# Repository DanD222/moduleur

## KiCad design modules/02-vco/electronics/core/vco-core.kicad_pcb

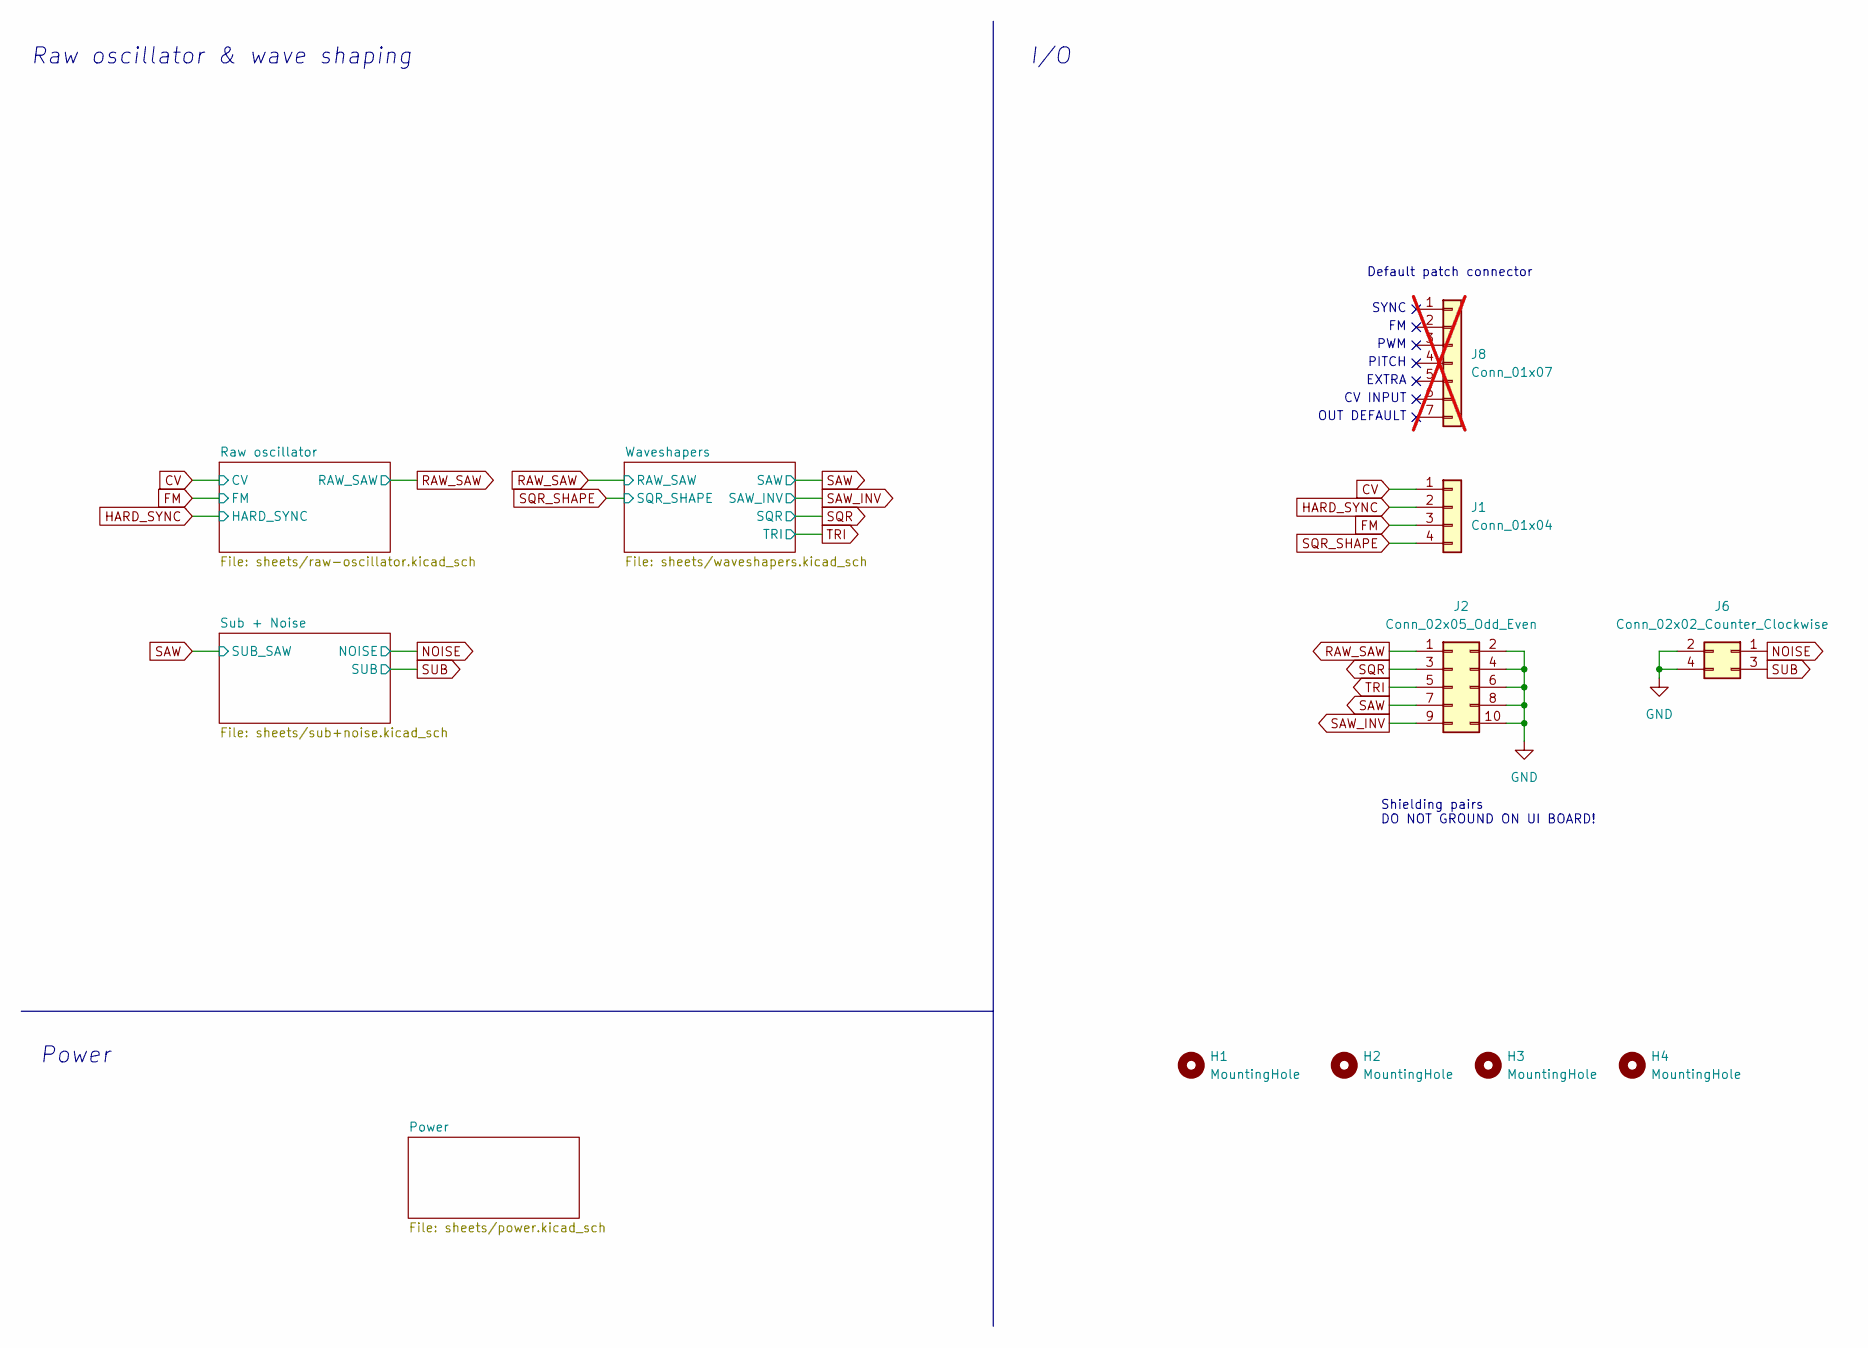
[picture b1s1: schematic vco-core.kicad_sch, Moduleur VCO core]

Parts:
H1, H2, H3, H4: MountingHole; MountingHole_3.2mm_M3_DIN965_Pad
J1: Conn_01x04; PinHeader_1x04_P2.54mm_Vertical; Mouser Part no. 200-HTSW10407TS
J2: Conn_02x05_Odd_Even; PinHeader_2x05_P2.54mm_Vertical; Mouser Part no. 200-TSW10507TD
J6: Conn_02x02_Counter_Clockwise; PinHeader_2x02_P2.54mm_Vertical; Mouser Part no. 200-HTSW10207TD
J8: Conn_01x07; PinHeader_1x07_P2.54mm_Vertical; Mouser Part no. 474-PRT-09280; not fitted

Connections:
CV: J1.1; also elsewhere on the board
FM: J1.3; also elsewhere on the board
GND: J2.2, J2.4, J2.6, J2.8, J2.10, J6.2, J6.4; also elsewhere on the board
HARD_SYNC: J1.2; also elsewhere on the board
NOISE: J6.1; also elsewhere on the board
RAW_SAW: J2.1; also elsewhere on the board
SAW: J2.7; also elsewhere on the board
SAW_INV: J2.9; also elsewhere on the board
SQR: J2.3; also elsewhere on the board
SUB: J6.3; also elsewhere on the board
TRI: J2.5; also elsewhere on the board

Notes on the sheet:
Power
PWM
Default patch connector
CV INPUT
SYNC
OUT DEFAULT
Shielding pairs DO NOT GROUND ON UI BOARD!
EXTRA
Raw oscillator & wave shaping
I/O
PITCH

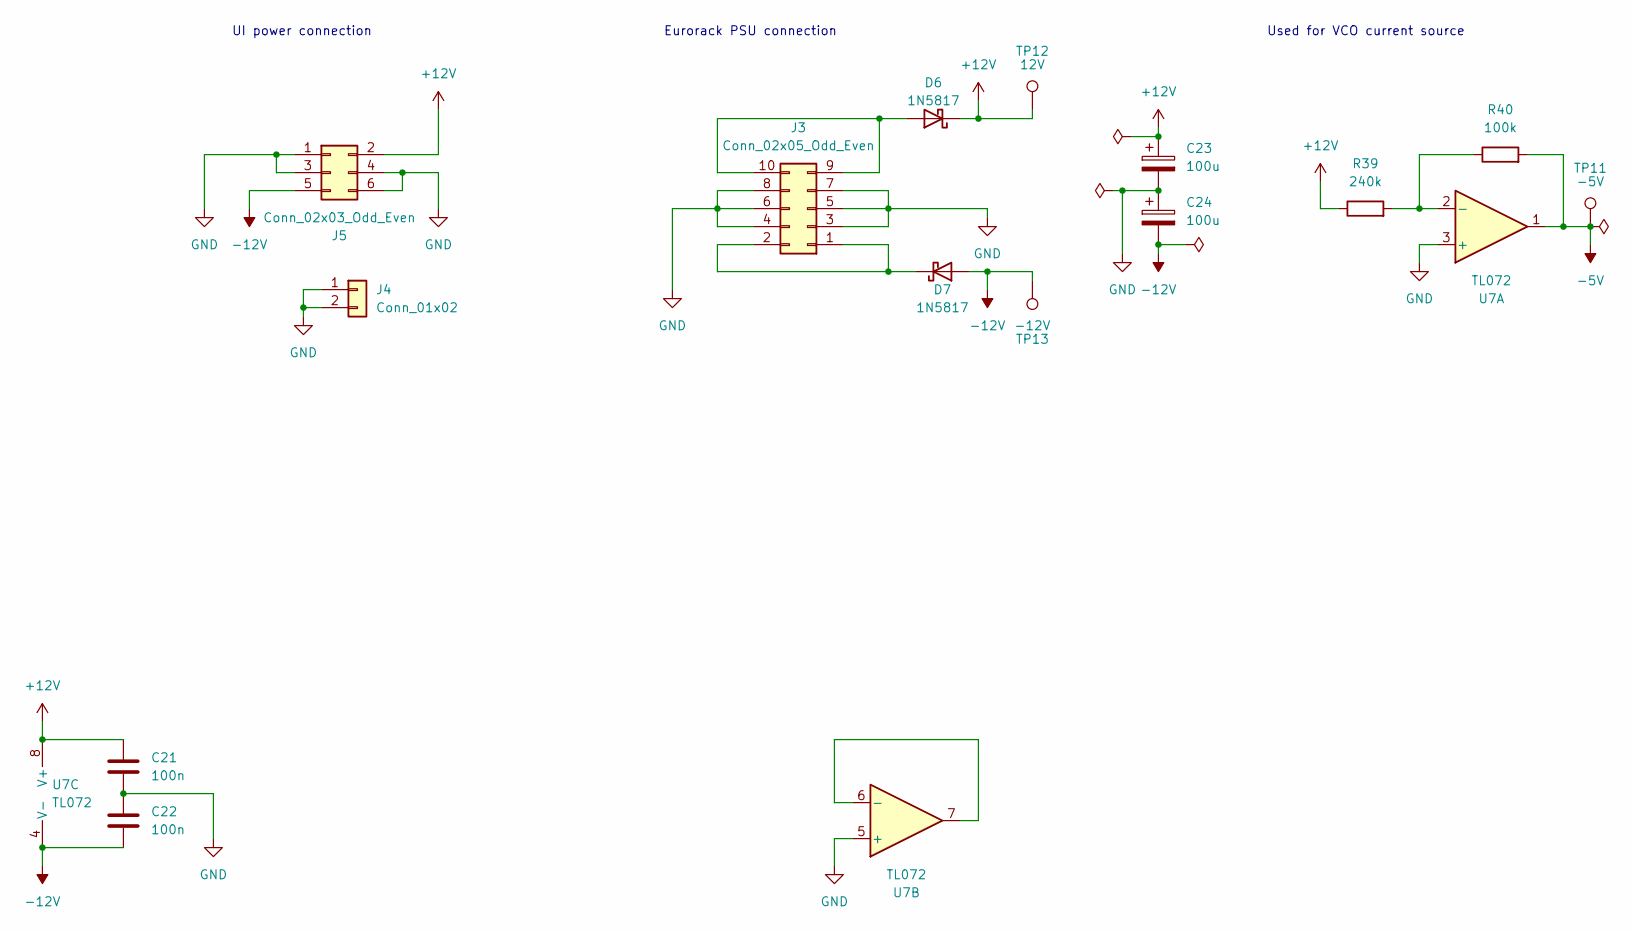
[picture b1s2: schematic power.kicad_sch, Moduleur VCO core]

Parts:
C21, C22: 100n; C_0603_1608Metric; LCSC C14663
C23, C24: 100u; CP_Elec_6.3x7.7; LCSC C2836442
D6, D7: 1N5817; D_SOD-323; LCSC C5190152
J3: Conn_02x05_Odd_Even; IDC-Header_2x05_P2.54mm_Horizontal; Mouser Part no. 571-5103310-1
J4: Conn_01x02; PinHeader_1x02_P2.54mm_Vertical; Mouser Part no. 200-HTSW10207TS
J5: Conn_02x03_Odd_Even; PinHeader_2x03_P2.54mm_Vertical; Mouser Part no. 200-TSW10307TD
R39: 240k; R_0603_1608Metric; LCSC C4197
R40: 100k; R_0603_1608Metric; LCSC C25803
TP11: -5V; TestPoint_THTPad_2.0x2.0mm_Drill1.0mm
TP12: 12V; TestPoint_THTPad_2.0x2.0mm_Drill1.0mm
TP13: -12V; TestPoint_THTPad_2.0x2.0mm_Drill1.0mm
U7: TL072; SOIC-8_3.9x4.9mm_P1.27mm; LCSC C6961

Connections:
-5V: R40.2, TP11.1 (1_1), U7.1; also elsewhere on the board
GND: C21.2, C22.1, C23.2, C24.1, J3.3, J3.4, J3.5, J3.6, J3.7, J3.8, J4.1, J4.2, J5.1, J5.3, J5.4, J5.6, U7.3 (+), U7.5 (+); also elsewhere on the board
unnamed: D6.2 (A), J3.9, J3.10
unnamed: D7.1 (K), J3.1, J3.2
unnamed: R39.2, R40.1, U7.2 (-)
unnamed: U7.6 (-), U7.7

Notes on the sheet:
UI power connection
Eurorack PSU connection
Used for VCO current source

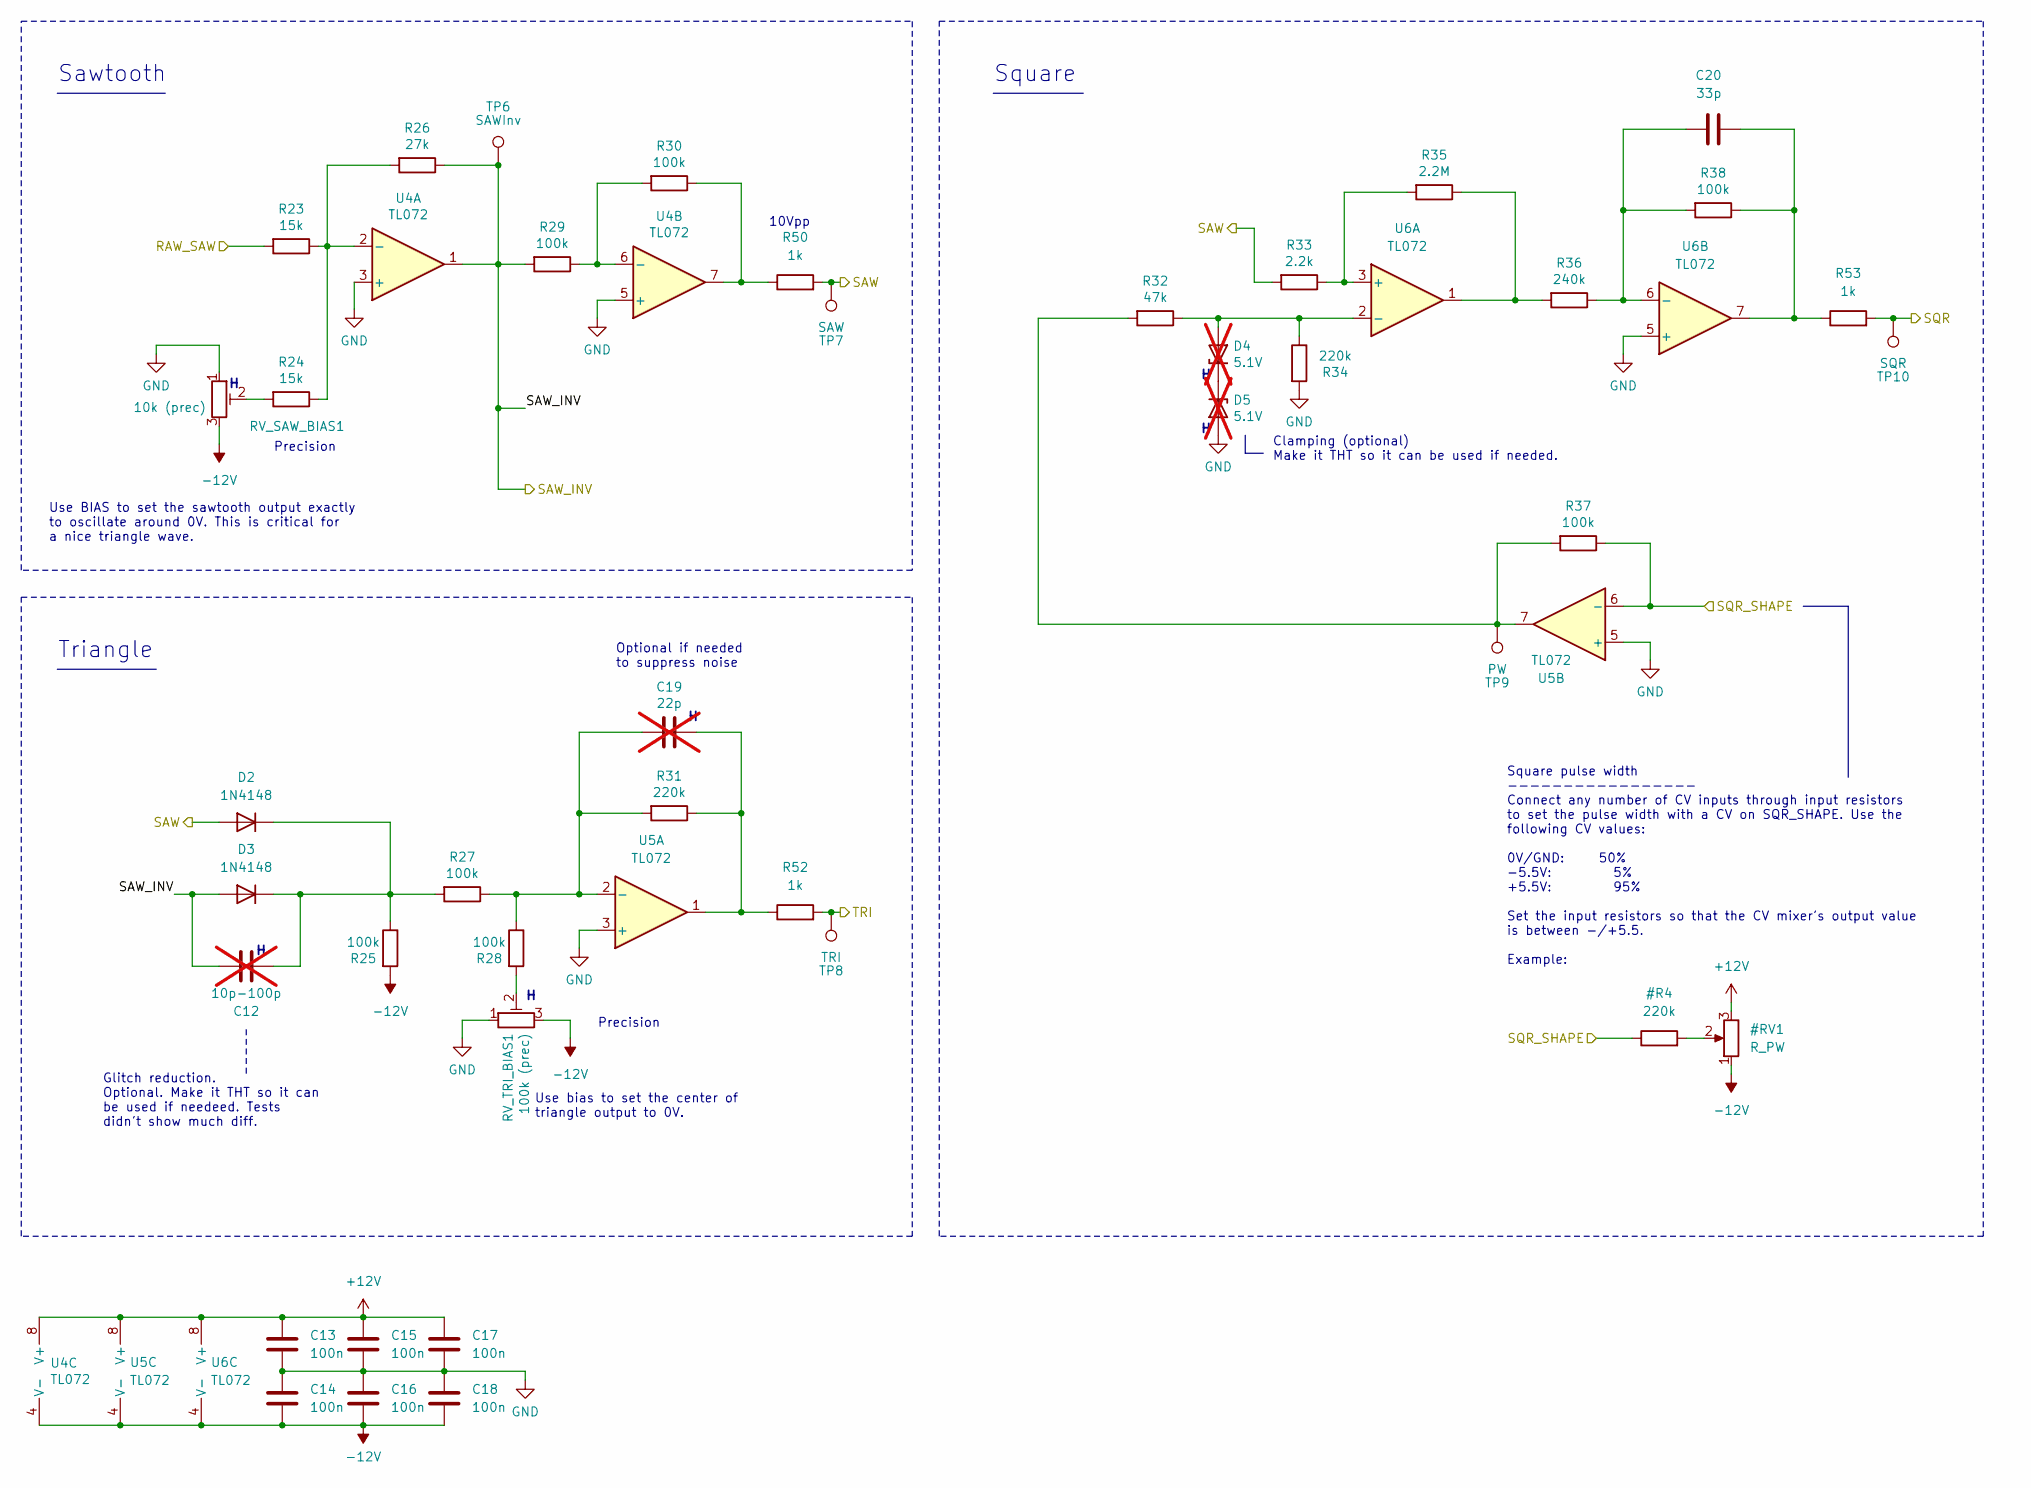
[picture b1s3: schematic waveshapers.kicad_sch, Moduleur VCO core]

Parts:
C12: 10p-100p; C_Rect_L7.0mm_W2.5mm_P5.00mm; not fitted
C13, C14, C15, C16, C17, C18: 100n; C_0603_1608Metric; LCSC C14663
C19: 22p; C_Disc_D3.0mm_W2.0mm_P2.50mm; not fitted
C20: 33p; C_0603_1608Metric; LCSC C1663
D2, D3: 1N4148; D_SOD-123; LCSC C81598
D4, D5: 5.1V; D_DO-34_SOD68_P2.54mm_Vertical_AnodeUp; not fitted
R23, R24: 15k; R_0603_1608Metric; LCSC C22809
R25, R27, R28, R29, R30, R37, R38: 100k; R_0603_1608Metric; LCSC C25803
R26: 27k; R_0603_1608Metric; LCSC C22967
R31, R34: 220k; R_0603_1608Metric; LCSC C22961
R32: 47k; R_0603_1608Metric; LCSC C25819
R33: 2.2k; R_0603_1608Metric; LCSC C4190
R35: 2.2M; R_0603_1608Metric; LCSC C18679
R36: 240k; R_0603_1608Metric; LCSC C4197
R50, R52, R53: 1k; R_0603_1608Metric; LCSC C21190
RV_SAW_BIAS1: 10k (prec); Potentiometer_Bourns_3006P_Horizontal; Mouser Part no. 652-3006P-1-103-LF
RV_TRI_BIAS1: 100k (prec); Potentiometer_Bourns_3006P_Horizontal; Mouser Part no. 652-3006P-1-104-LF
TP6: SAWInv; TestPoint_THTPad_2.0x2.0mm_Drill1.0mm
TP7: SAW; TestPoint_THTPad_2.0x2.0mm_Drill1.0mm
TP8: TRI; TestPoint_THTPad_2.0x2.0mm_Drill1.0mm
TP9: PW; TestPoint_THTPad_2.0x2.0mm_Drill1.0mm
TP10: SQR; TestPoint_THTPad_2.0x2.0mm_Drill1.0mm
U4, U5, U6: TL072; SOIC-8_3.9x4.9mm_P1.27mm; LCSC C6961

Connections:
GND: C13.2, C14.1, C15.2, C16.1, C17.2, C18.1, D5.2 (A), R34.2, RV_SAW_BIAS1.1, RV_TRI_BIAS1.1, U4.3 (+), U4.5 (+), U5.3 (+), U5.5 (+), U6.5 (+); also elsewhere on the board
unnamed: C19.1, R31.1, R52.1, U5.1
unnamed: C20.2, R38.1, R53.1, U6.7
unnamed: C12.1, D2.1 (K), D3.1 (K), R25.1, R27.2
unnamed: D4.2 (A), R32.1, R34.1, U6.2 (-)
unnamed: D4.1 (K), D5.1 (K)
unnamed: R24.2, RV_SAW_BIAS1.2
unnamed: R28.2, RV_TRI_BIAS1.2
unnamed: R30.1, R50.1, U4.7
unnamed: R32.2, R37.2, TP9.1 (1_1), U5.7
unnamed: R35.1, R36.2, U6.1
unnamed: R23.1, R24.1, R26.2, U4.2 (-)
unnamed: R29.1, R30.2, U4.6 (-)
unnamed: C19.2, R27.1, R28.1, R31.2, U5.2 (-)
unnamed: R33.1, R35.2, U6.3 (+)
unnamed: C20.1, R36.1, R38.2, U6.6 (-)
RAW_SAW: R23.2; also elsewhere on the board
SAW: D2.2 (A), R33.2, R50.2, TP7.1 (1_1); also elsewhere on the board
SAW_INV: C12.2, D3.2 (A), R26.1, R29.2, TP6.1 (1_1), U4.1; also elsewhere on the board
SQR: R53.2, TP10.1 (1_1); also elsewhere on the board
TRI: R52.2, TP8.1 (1_1); also elsewhere on the board

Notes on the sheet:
Use bias to set the center of triangle output to 0V.
Clamping (optional) Make it THT so it can be used if needed.
Use BIAS to set the sawtooth output exactly to oscillate around 0V. This is critical for a nice triangle wave.
Sawtooth
Precision
10Vpp
Square pulse width ----------------- Connect any number of CV inputs through input resistors to set the pulse width with a CV on SQR_SHAPE. Use the following CV values: 0V/GND: 50% -5.5V: 5% +5.5V: 95% Set the input resistors so that the CV mixer's output value is between -/+5.5. Example:
Square
Optional if needed to suppress noise
Glitch reduction. Optional. Make it THT so it can be used if needeed. Tests didn't show much diff.
Triangle

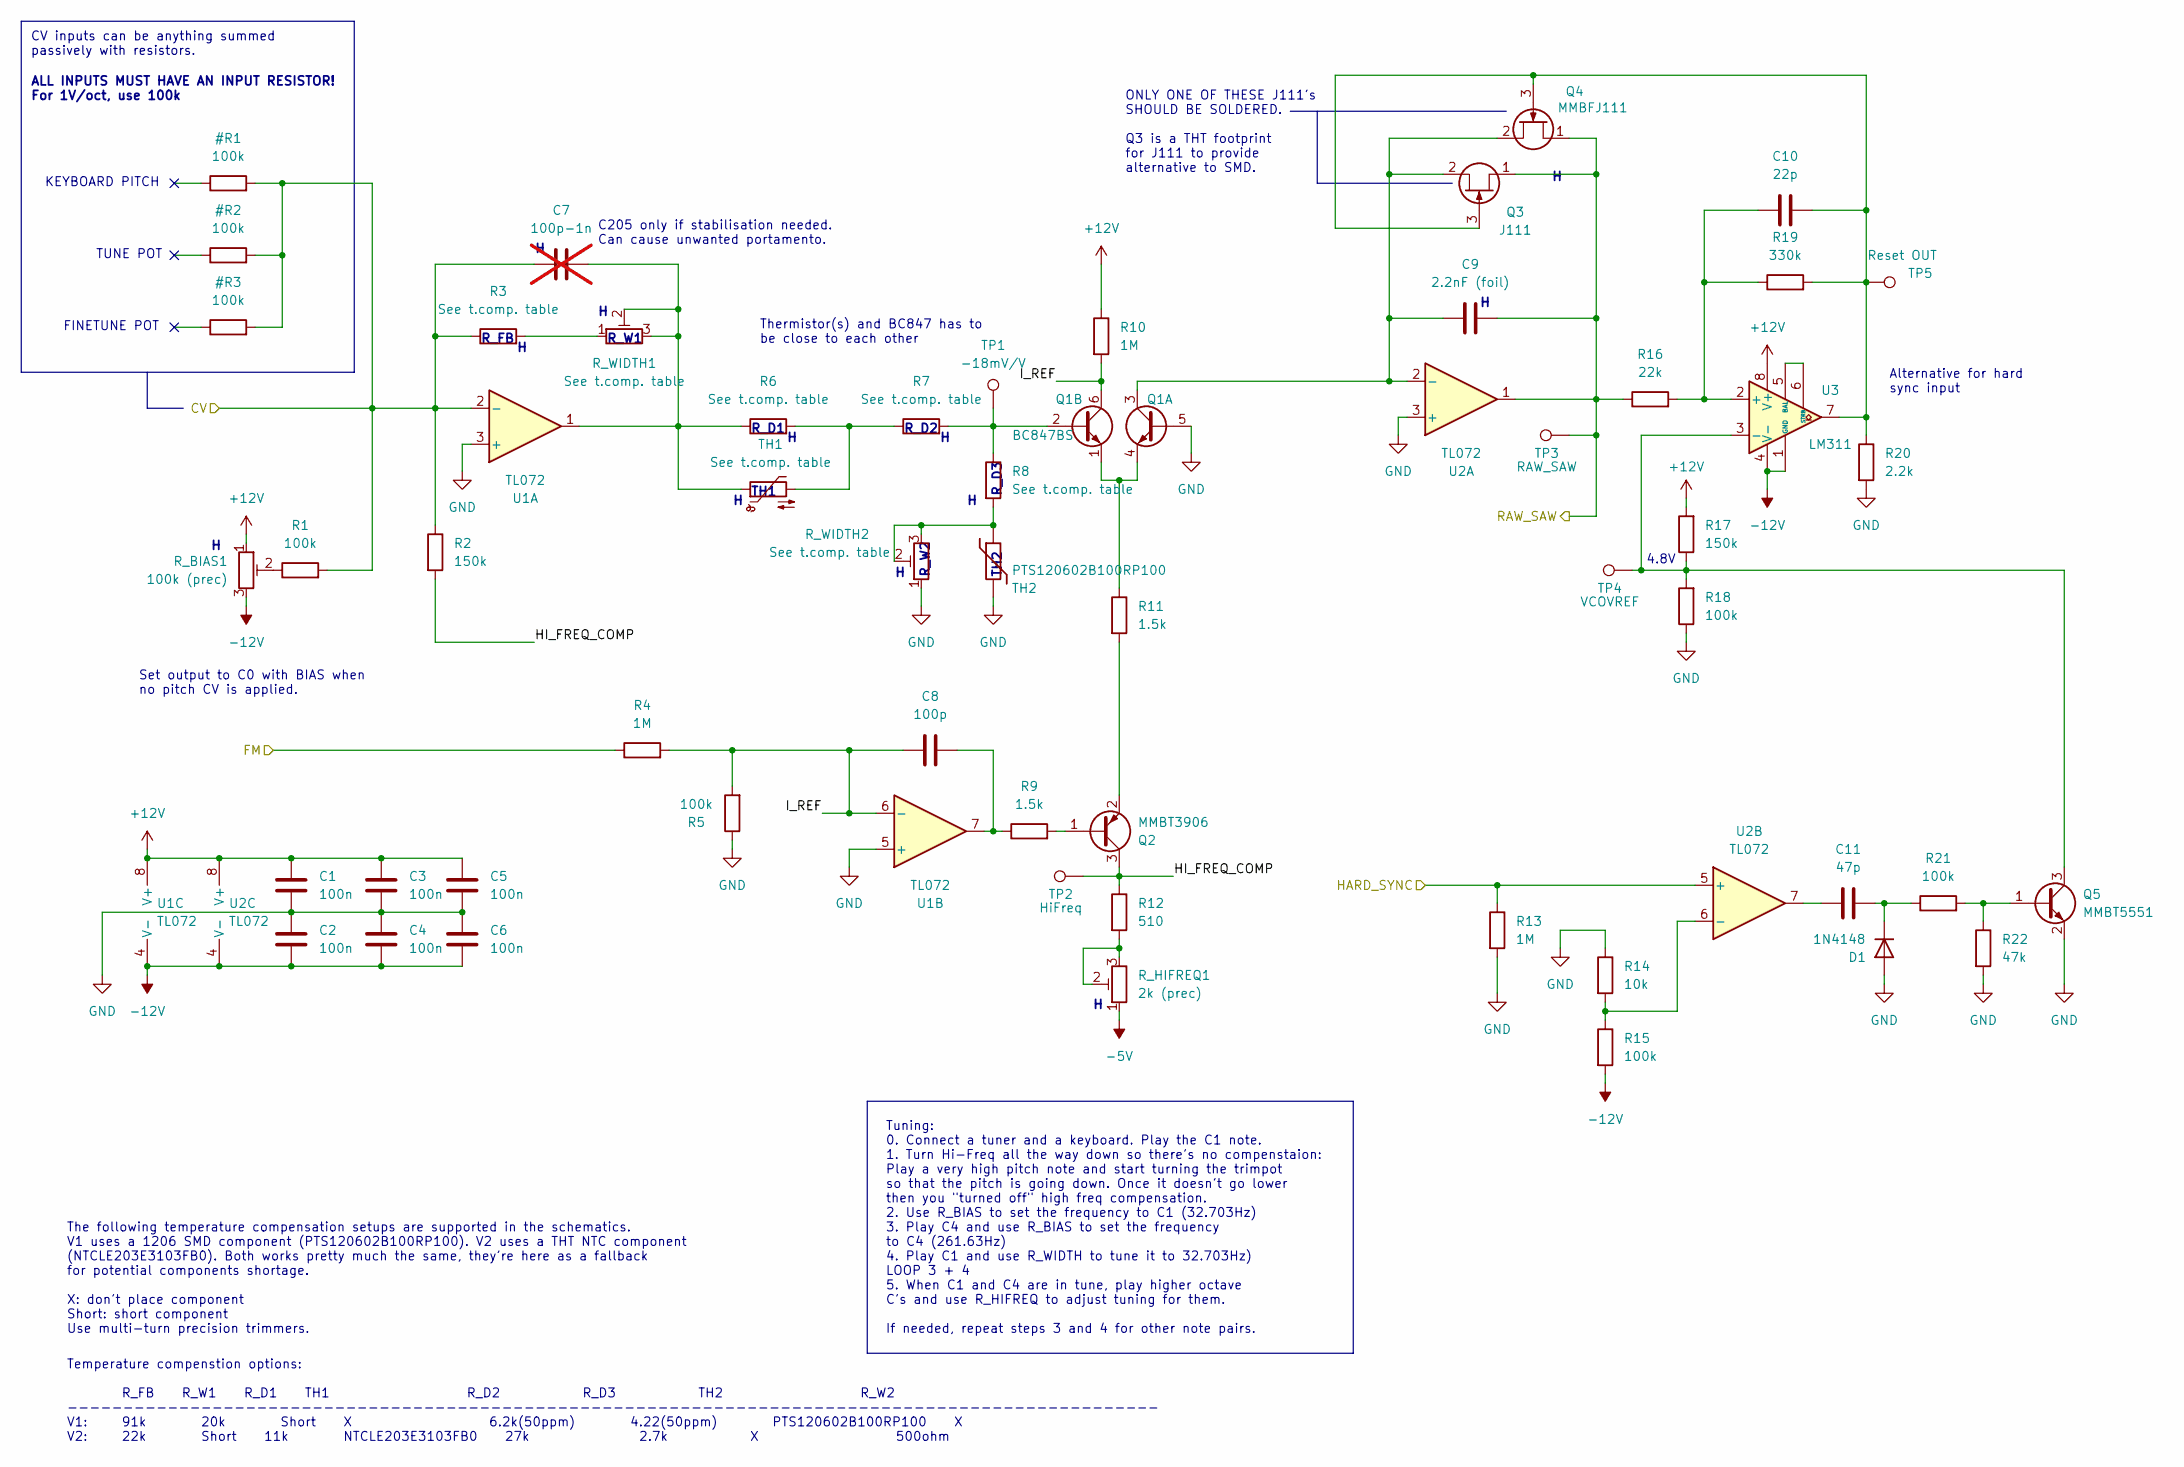
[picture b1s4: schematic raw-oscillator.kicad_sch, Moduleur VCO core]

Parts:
C1, C2, C3, C4, C5, C6: 100n; C_0603_1608Metric; LCSC C14663
C7: 100p-1n; C_Disc_D3.0mm_W1.6mm_P2.50mm; not fitted
C8: 100p; C_0603_1608Metric; LCSC C14858
C9: 2.2nF (foil); C_Rect_L7.2mm_W2.5mm_P5.00mm_FKS2_FKP2_MKS2_MKP2; Mouser Part no. 80-R82MC1220AA50J
C10: 22p; C_0603_1608Metric; LCSC C1653
C11: 47p; C_0603_1608Metric; LCSC C1671
D1: 1N4148; D_SOD-123; LCSC C81598
Q1: BC847BS; SOT-363_SC-70-6; LCSC C5380687
Q2: MMBT3906; SOT-23; LCSC C53444
Q3: J111; TO-92_Inline_Wide; Mouser Part no. 512-J111
Q4: MMBFJ111; SOT-23; LCSC C274688
Q5: MMBT5551; SOT-23; LCSC C2145
R1, R5, R15, R18, R21: 100k; R_0603_1608Metric; LCSC C25803
R2, R17: 150k; R_0603_1608Metric; LCSC C22807
R3, R6, R7, R8: See t.comp. table; R_Axial_DIN0207_L6.3mm_D2.5mm_P7.62mm_Horizontal
R4, R10, R13: 1M; R_0603_1608Metric; LCSC C22935
R9, R11: 1.5k; R_0603_1608Metric; LCSC C22843
R12: 510; R_0603_1608Metric; LCSC C23193
R14: 10k; R_0603_1608Metric; LCSC C25804
R16: 22k; R_0603_1608Metric; LCSC C31850
R19: 330k; R_0603_1608Metric; LCSC C23137
R20: 2.2k; R_0603_1608Metric; LCSC C4190
R22: 47k; R_0603_1608Metric; LCSC C25819
R_BIAS1: 100k (prec); Potentiometer_Bourns_3006P_Horizontal; Mouser Part no. 652-3006P-1-104-LF
R_HIFREQ1: 2k (prec); Potentiometer_Bourns_3006P_Horizontal; Mouser Part no. 652-3006P-1-202-LF
R_WIDTH1: See t.comp. table; Potentiometer_Bourns_3006P_Horizontal; Mouser Part no. 652-3006P-7-203-LF
R_WIDTH2: See t.comp. table; Potentiometer_Bourns_3006P_Horizontal; Mouser Part no. 652-3006P-1-501-LF
TH1: See t.comp. table; TO-92-2; Mouser Part no. 594-2381-640-55103
TH2: PTS120602B100RP100; R_1206_3216Metric_Pad1.30x1.75mm_HandSolder; Mouser Part no. 594-PTS120601B100RP
TP1: -18mV/V; TestPoint_THTPad_2.0x2.0mm_Drill1.0mm
TP2: HiFreq; TestPoint_THTPad_2.0x2.0mm_Drill1.0mm
TP3: RAW_SAW; TestPoint_THTPad_2.0x2.0mm_Drill1.0mm
TP4: VCOVREF; TestPoint_THTPad_2.0x2.0mm_Drill1.0mm
TP5: Reset OUT; TestPoint_THTPad_2.0x2.0mm_Drill1.0mm
U1, U2: TL072; SOIC-8_3.9x4.9mm_P1.27mm; LCSC C6961
U3: LM311; SOIC-8_3.9x4.9mm_P1.27mm; LCSC C12597

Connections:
-5V: R_HIFREQ1.1; also elsewhere on the board
/Raw oscillator/HI_FREQ_COMP: Q2.3 (C), R2.2, R12.1, TP2.1 (1_1)
/Raw oscillator/I_REF: C8.1, Q1.6 (C1), R4.2, R5.2, R10.2, U1.6 (-)
CV: C7.1, R1.2, R2.1, R3.1, U1.2 (-); also elsewhere on the board
FM: R4.1; also elsewhere on the board
GND: C1.2, C2.1, C3.2, C4.1, C5.2, C6.1, D1.2 (A), Q1.5 (B2), Q5.2 (E), R5.1, R13.2, R14.1, R18.1, R20.2, R22.2, R_WIDTH2.1, TH2.2, U1.3 (+), U1.5 (+), U2.3 (+); also elsewhere on the board
HARD_SYNC: R13.1, U2.5 (+); also elsewhere on the board
unnamed: C7.2, R6.1, R_WIDTH1.2, R_WIDTH1.3, TH1.1, U1.1
unnamed: C8.2, R9.1, U1.7
unnamed: C11.1, U2.7
unnamed: C11.2, D1.1 (K), R21.1
unnamed: Q1.2 (B1), R7.2, R8.1, TP1.1 (1_1)
unnamed: Q1.1 (E1), Q1.4 (E2), R11.1
unnamed: C9.1, Q1.3 (C2), Q3.2 (S), Q4.2 (S), U2.2 (-)
unnamed: Q2.1 (B), R9.2
unnamed: Q2.2 (E), R11.2
unnamed: C10.2, Q3.3 (G), Q4.3 (G), R19.2, R20.1, TP5.1 (1_1), U3.7
unnamed: Q5.1 (B), R21.2, R22.1
unnamed: Q5.3 (C), R17.1, R18.2, TP4.1 (1_1), U3.3 (-)
unnamed: R1.1, R_BIAS1.2
unnamed: R3.2, R_WIDTH1.1
unnamed: R6.2, R7.1, TH1.2
unnamed: R8.2, R_WIDTH2.2, R_WIDTH2.3, TH2.1
unnamed: R12.2, R_HIFREQ1.2, R_HIFREQ1.3
unnamed: R14.2, R15.1, U2.6 (-)
unnamed: C10.1, R16.2, R19.1, U3.2 (+)
unnamed: U3.5 (BAL), U3.6 (STRB)
RAW_SAW: C9.2, Q3.1 (D), Q4.1 (D), R16.1, TP3.1 (1_1), U2.1; also elsewhere on the board

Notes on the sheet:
ONLY ONE OF THESE J111's SHOULD BE SOLDERED. Q3 is a THT footprint for J111 to provide alternative to SMD.
R_W2
TH2
Tuning: 0. Connect a tuner and a keyboard. Play the C1 note. 1. Turn Hi-Freq all the way down so there's no compenstaion: Play a very high pitch note and start turning the trimpot so that the pitch is going down. Once it doesn't go lower then you "turned off" high freq compensation. 2. Use R_BIAS t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
R_W1
C205 only if stabilisation needed. Can cause unwanted portamento.
Thermistor(s) and BC847 has to be close to each other
ALL INPUTS MUST HAVE AN INPUT RESISTOR! For 1V/oct, use 100k
Alternative for hard sync input
Temperature compenstion options: R_FB R_W1 R_D1 TH1 R_D2 R_D3 TH2 R_W2 -------------------------------------------------------------------------------------------------- V1: 91k 20k Short X 6.2k(50ppm) 4.22(50ppm) PTS120602B100RP100 X V2: 22k Short 11k NTCLE203E3103FB0 27k 2.7k X 500ohm
CV inputs can be anything summed passively with resistors.
KEYBOARD PITCH
TUNE POT
The following temperature compensation setups are supported in the schematics. V1 uses a 1206 SMD component (PTS120602B100RP100). V2 uses a THT NTC component (NTCLE203E3103FB0). Both works pretty much the same, they're here as a fallback for potential components shortage. X: don't place component S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
TH1
R_FB
FINETUNE POT
R_D3
R_D1
Set output to C0 with BIAS when no pitch CV is applied.
R_D2
4.8V

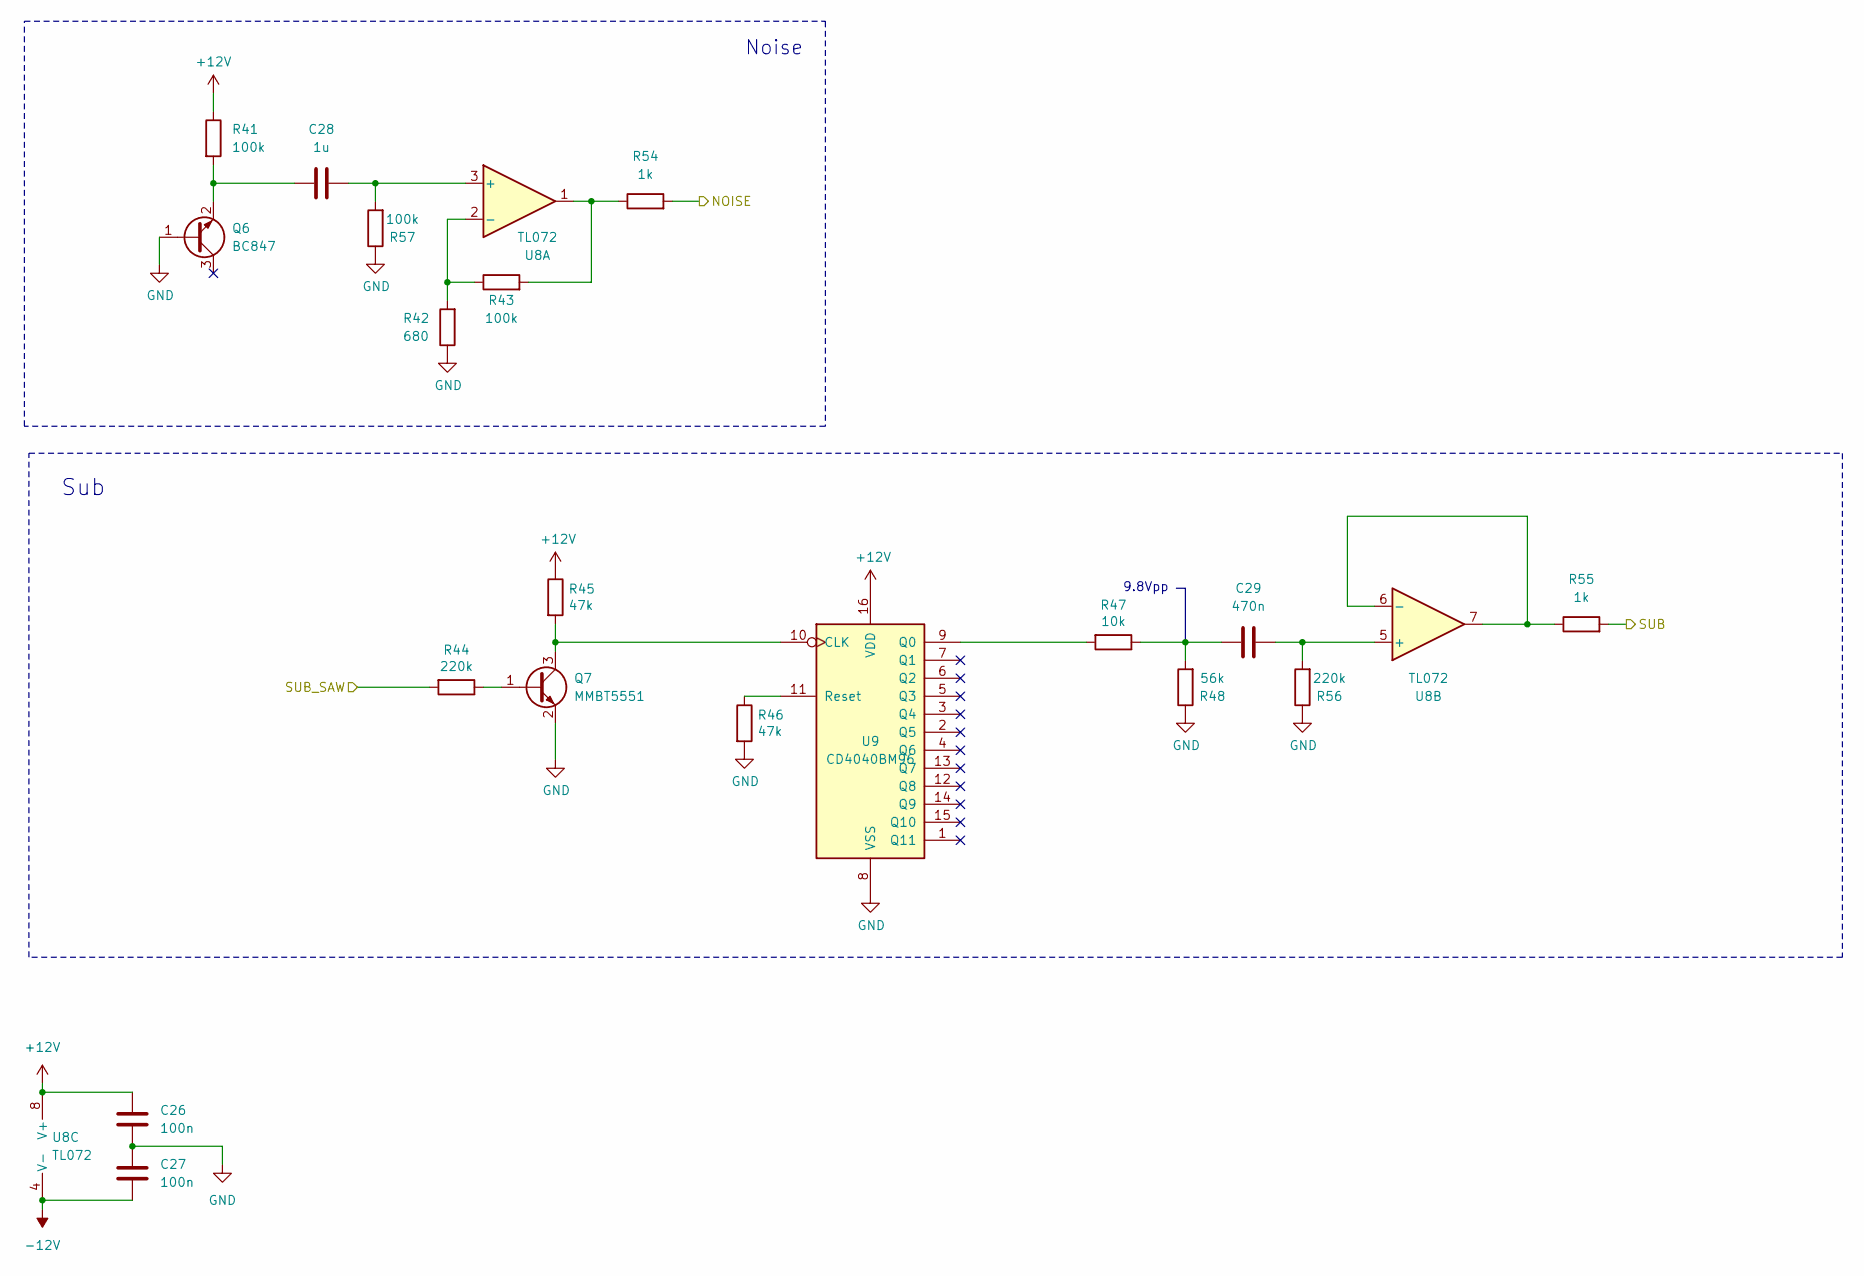
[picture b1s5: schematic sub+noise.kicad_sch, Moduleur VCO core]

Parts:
C26, C27: 100n; C_0603_1608Metric; LCSC C14663
C28: 1u; C_0603_1608Metric; LCSC C15849
C29: 470n; C_Rect_L7.2mm_W3.5mm_P5.00mm_FKS2_FKP2_MKS2_MKP2; Mouser Part no. 80-R82DC3470DQ60K
Q6: BC847; SOT-23; LCSC C8664
Q7: MMBT5551; SOT-23; LCSC C2145
R41, R43, R57: 100k; R_0603_1608Metric; LCSC C25803
R42: 680; R_0603_1608Metric; LCSC C23228
R44, R56: 220k; R_0603_1608Metric; LCSC C22961
R45, R46: 47k; R_0603_1608Metric; LCSC C25819
R47: 10k; R_0603_1608Metric; LCSC C25804
R48: 56k; R_0603_1608Metric; LCSC C23206
R54, R55: 1k; R_0603_1608Metric; LCSC C21190
U8: TL072; SOIC-8_3.9x4.9mm_P1.27mm; LCSC C6961
U9: CD4040BM96; SOIC-16_3.9x9.9mm_P1.27mm; LCSC C353974

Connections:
GND: C26.2, C27.1, Q6.1 (B), Q7.2 (E), R42.1, R46.2, R48.1, R56.1, R57.1, U9.8 (VSS); also elsewhere on the board
NOISE: R54.2; also elsewhere on the board
unnamed: C29.1, R47.1, R48.2
unnamed: C28.1, Q6.2 (E), R41.2
unnamed: Q7.1 (B), R44.1
unnamed: Q7.3 (C), R45.2, U9.10 (CLK)
unnamed: R43.2, R54.1, U8.1
unnamed: C28.2, R57.2, U8.3 (+)
unnamed: R42.2, R43.1, U8.2 (-)
unnamed: C29.2, R56.2, U8.5 (+)
unnamed: R55.1, U8.6 (-), U8.7
unnamed: R47.2, U9.9 (Q0)
unnamed: R46.1, U9.11 (Reset)
SAW: R44.2; also elsewhere on the board
SUB: R55.2; also elsewhere on the board

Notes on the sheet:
Noise
9.8Vpp
Sub

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
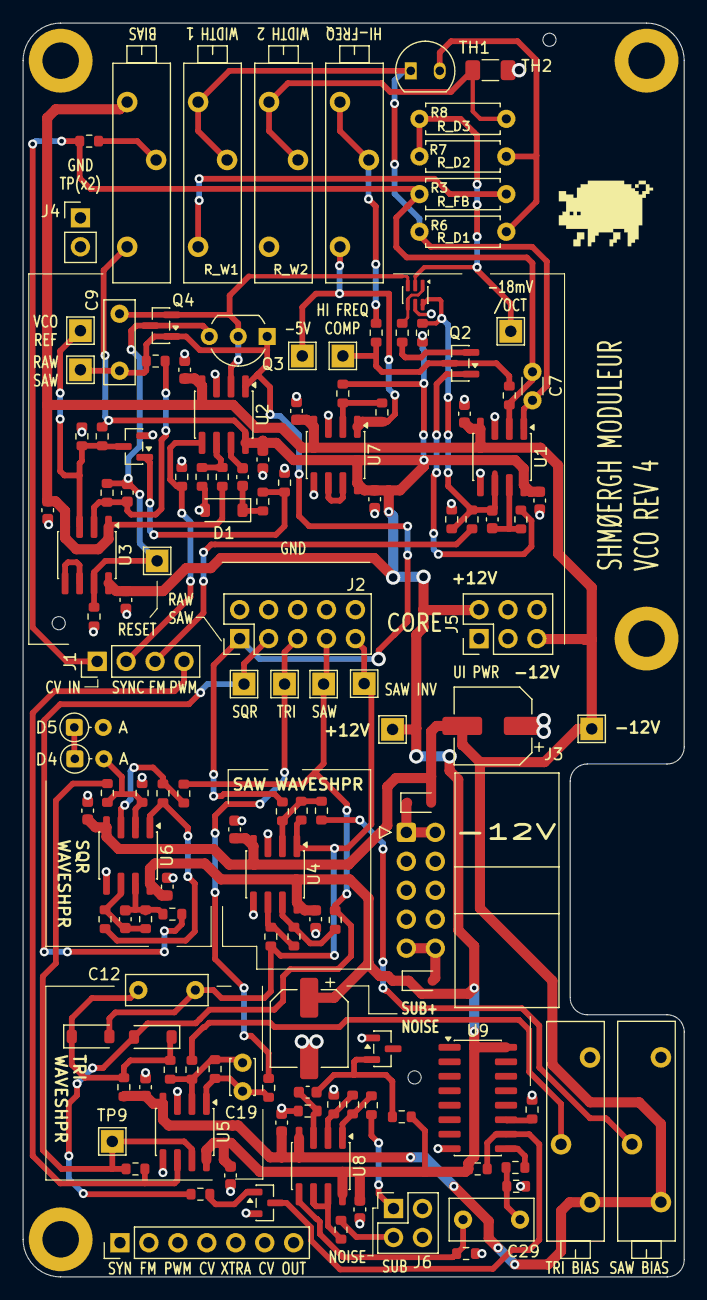
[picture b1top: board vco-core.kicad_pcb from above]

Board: 2 copper layers, 58.0 x 110.0 mm, 138 parts (0 on the bottom side), 67 nets.

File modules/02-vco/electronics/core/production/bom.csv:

Designator,Footprint,Quantity,Value,LCSC Part #
"C1, C13, C14, C15, C16, C17, C18, C2, C21, C22, C26, C27, C3, C4, C5, C6",0603,16,100n,C14663
C10,0603,1,22p,C1653
C11,0603,1,47p,C1671
C20,0603,1,33p,C1663
"C23, C24",CP_Elec_6.3x7.7,2,100u,C2836442
C28,0603,1,1u,C15849
C29,C_Rect_L7.2mm_W3.5mm_P5.00mm_FKS2_FKP2_MKS2_MKP2,1,470n,
C8,0603,1,100p,C14858
C9,C_Rect_L7.2mm_W2.5mm_P5.00mm_FKS2_FKP2_MKS2_MKP2,1,2.2nF (foil),
"D1, D2, D3",D_SOD-123,3,1N4148,C81598
"D6, D7",D_SOD-323,2,1N5817,C5190152
J1,PinHeader_1x04_P2.54mm_Vertical,1,Conn_01x04,
J2,PinHeader_2x05_P2.54mm_Vertical,1,Conn_02x05_Odd_Even,
J3,IDC-Header_2x05_P2.54mm_Horizontal,1,Conn_02x05_Odd_Even,
J4,PinHeader_1x02_P2.54mm_Vertical,1,Conn_01x02,
J5,PinHeader_2x03_P2.54mm_Vertical,1,Conn_02x03_Odd_Even,
J6,PinHeader_2x02_P2.54mm_Vertical,1,Conn_02x02_Counter_Clockwise,
J8,PinHeader_1x07_P2.54mm_Vertical,1,Conn_01x07,
Q1,SOT-363_SC-70-6,1,BC847BS,C5380687
Q2,SOT-23,1,MMBT3906,C53444
Q3,TO-92_Inline_Wide,1,J111,
Q4,SOT-23,1,MMBFJ111,C274688
"Q5, Q7",SOT-23,2,MMBT5551,C2145
Q6,SOT-23,1,BC847,C8664
"R1, R15, R18, R21, R25, R27, R28, R29, R30, R37, R38, R40, R41, R43, R5, R57",0603,16,100k,C25803
"R10, R13, R4",0603,3,1M,C22935
"R11, R9",0603,2,1.5k,C22843
R12,0603,1,510,C23193
"R14, R47",0603,2,10k,C25804
R16,0603,1,22k,C31850
"R17, R2",0603,2,150k,C22807
R19,0603,1,330k,C23137
"R20, R33",0603,2,2.2k,C4190
"R22, R32, R45, R46",0603,4,47k,C25819
"R23, R24",0603,2,15k,C22809
R26,0603,1,27k,C22967
"R3, R6, R7, R8",R_Axial_DIN0207_L6.3mm_D2.5mm_P7.62mm_Horizontal,4,See t.comp. table,
"R31, R34, R44, R56",0603,4,220k,C22961
R35,0603,1,2.2M,C18679
"R36, R39",0603,2,240k,C4197
R42,0603,1,680,C23228
R48,0603,1,56k,C23206
"R50, R52, R53, R54, R55",0603,5,1k,C21190
RV_SAW_BIAS1,Potentiometer_Bourns_3006P_Horizontal,1,10k (prec),
"RV_TRI_BIAS1, R_BIAS1",Potentiometer_Bourns_3006P_Horizontal,2,100k (prec),
R_HIFREQ1,Potentiometer_Bourns_3006P_Horizontal,1,2k (prec),
"R_WIDTH1, R_WIDTH2",Potentiometer_Bourns_3006P_Horizontal,2,See t.comp. table,
TH1,TO-92-2,1,See t.comp. table,
TH2,1206,1,PTS120602B100RP100,
"U1, U2, U4, U5, U6, U7, U8",SOIC-8_3.9x4.9mm_P1.27mm,7,TL072,C6961
U3,SOIC-8_3.9x4.9mm_P1.27mm,1,LM311,C12597
U9,SOIC-16_3.9x9.9mm_P1.27mm,1,CD4040BM96,C353974

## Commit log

2026-05-19 Enhance README with detailed tuning instructions
    Expanded explanation of sidechain compressor settings and VCA bias.
2026-05-23 Reverted KiCad 10 update because of faulty VCO Core
2026-05-23 Updated experimental VCO Core
2026-05-23 Revert "Updated experimental VCO Core"
    This reverts commit 34f3e113d18d89390407e9554ee904153359fd81.
2026-05-23 Revert "Reverted KiCad 10 update because of faulty VCO Core"
    This reverts commit 2181cec2415da0927836b64670f1fdf3fa70bf64.
2026-05-23 Reverted VCO Core back to latest stable
    - The latest working version of the VCO is this: (commit: https://github.com/shmoergh/moduleur/tree/b8f2f3887ee0ce40083da4d1238f04f5c6e473fa). Somewhere
    between January 24 and May 24 the PCB got corrupted and it doesn't work properly. It could be the KiCAD 10 migration.
2026-05-24 Fix: Replace generic MMBT3906 with ON Semi for Q2
    Q2 is the actuator in the master current servo loop (U1B → Q2) that sets the tail current for the exponential converter. The previous BOM specified the generic LCSC part C7420354, which JLCPCB silent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
    The R+O datasheet only characterizes hFE at IC = −10 mA and above, with no minimum specified at low collector currents. The circuit operates Q2 at sub-milliamp currents, where the substituted part ha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
2026-05-24 Added FIXLOG to VCO core board
2026-05-24 Revise FIXLOG with May 24, 2026 updates
    Updated the fix log to reflect the new date and added warnings for untested fixes.
2026-05-24 Fixed Q2 footprint pin numbering
    Previous production used the SMD MMBT3906 with traces routed to the wrong pads, leaving the transistor operating in reverse-active mode. This barely worked with some manufacturer's parts and failed e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
    For further information and manual fix, refer to VCO FIXLOG in the modules folder.
2026-05-24 Fixlog update
2026-05-24 Revise FIXLOG.md with updated repair instructions
    Updated the FIXLOG.md with detailed instructions for fixing faulty boards, including tested options and additional parts information.
2026-05-25 Revise fix instructions and update images for Q2
    Updated instructions for fixing faulty boards by adding details to OPTION 2 and replacing images.
2026-05-27 Re-exported VCO Core gerbers
